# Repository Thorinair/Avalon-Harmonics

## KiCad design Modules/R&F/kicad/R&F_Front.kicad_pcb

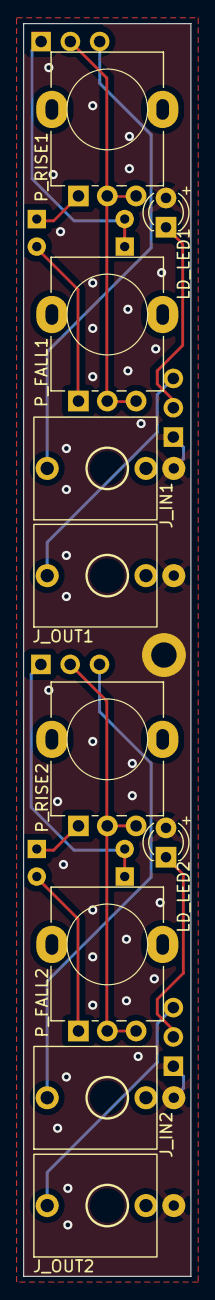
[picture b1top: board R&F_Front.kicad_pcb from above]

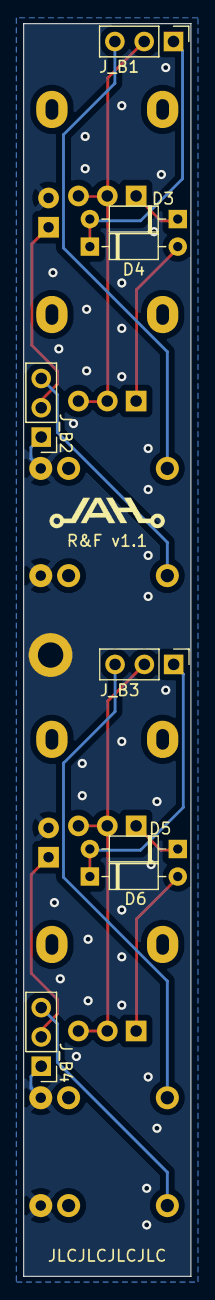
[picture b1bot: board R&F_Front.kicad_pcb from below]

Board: 2 copper layers, 14.5 x 108.6 mm, 18 parts (8 on the bottom side), 15 nets.

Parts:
D3, D4, D5, D6: 1N4148; D_DO-35_SOD27_P7.62mm_Horizontal
J_B1, J_B2, J_B3, J_B4: Conn_01x03_Female; PinHeader_1x03_P2.54mm_Vertical
J_IN1, J_IN2: PJ301M-12
J_OUT1, J_OUT2: PJ301M-12
LD_LED1, LD_LED2: LED (Bi); LED_D3.0mm_FlatTop
P_FALL1, P_FALL2: A1M; Potentiometer Alpha RD901F-40-00D
P_RISE1, P_RISE2: A1M; Potentiometer Alpha RD901F-40-00D

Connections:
GND: J_B2.1, J_B4.1, J_IN1.GND, J_IN2.GND, J_OUT1.GND, J_OUT2.GND, LD_LED1.2 (A), LD_LED2.2 (A)
unnamed: D3.1 (K), P_RISE1.1
unnamed: D3.2 (A), D4.1 (K), J_B1.1
unnamed: D4.2 (A), P_FALL1.1
unnamed: D5.1 (K), P_RISE2.1
unnamed: D5.2 (A), D6.1 (K), J_B3.1
unnamed: D6.2 (A), P_FALL2.1
unnamed: J_B1.2, P_FALL1.2, P_FALL1.3, P_RISE1.2, P_RISE1.3
unnamed: J_B1.3, J_IN1.SIG
unnamed: J_B2.2, LD_LED1.1 (K)
unnamed: J_B2.3, J_OUT1.SIG
unnamed: J_B3.2, P_FALL2.2, P_FALL2.3, P_RISE2.2, P_RISE2.3
unnamed: J_B3.3, J_IN2.SIG
unnamed: J_B4.2, LD_LED2.1 (K)
unnamed: J_B4.3, J_OUT2.SIG

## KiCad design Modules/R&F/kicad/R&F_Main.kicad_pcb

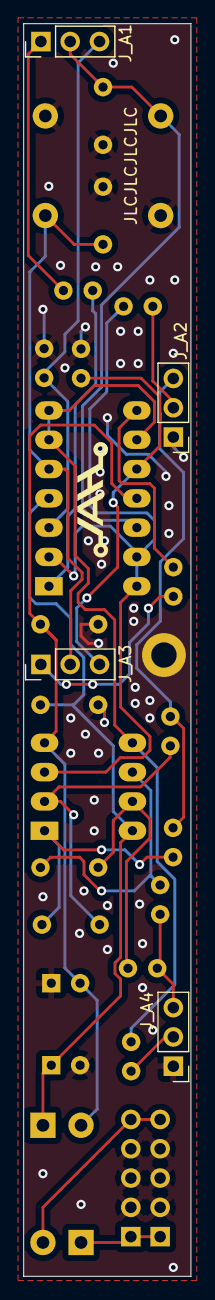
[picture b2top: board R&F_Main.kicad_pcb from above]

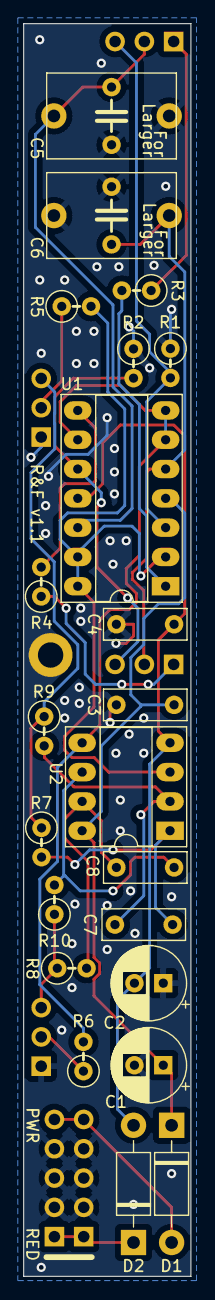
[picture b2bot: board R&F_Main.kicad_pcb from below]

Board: 2 copper layers, 14.5 x 108.6 mm, 27 parts (23 on the bottom side), 23 nets.

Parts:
C1, C2: 47uF; CP_Radial_D6.3mm_P2.50mm
C3, C4: 0.1uF; C_Disc_D7.0mm_W2.5mm_P5.00mm
C5, C6: 10uF (Film); C_Rect_L7.2mm_W11.0mm_P5.00mm_FKS2_FKP2_MKS2_MKP2_DUAL_SIZE
C7, C8: 100pF; C_Disc_D7.0mm_W2.5mm_P5.00mm
D1, D2: 1N4001; D_DO-41_SOD81_P10.16mm_Horizontal
J_A1, J_A2, J_A3, J_A4: Conn_01x03_Male; PinHeader_1x03_P2.54mm_Vertical
PWR1: PWR_10_Pin; Eurorack Power 10 Pin
R1, R2: 100k; R_Axial_DIN0207_L6.3mm_D2.5mm_P2.54mm_Vertical
R3, R4: 330; R_Axial_DIN0207_L6.3mm_D2.5mm_P2.54mm_Vertical
R5, R6, R7, R8: 1k; R_Axial_DIN0207_L6.3mm_D2.5mm_P2.54mm_Vertical
R9, R10: 4.7k; R_Axial_DIN0207_L6.3mm_D2.5mm_P2.54mm_Vertical
U1: TL074; DIP-14_W7.62mm_Socket_LongPads
U2: TL072; DIP-8_W7.62mm_Socket_LongPads

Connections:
+12V: C1.1, C3.1, D1.1 (K), U1.4 (V+), U2.8 (V+)
-12V: C2.2, C4.2, D2.2 (A), U1.11 (V-), U2.4 (V-)
/LED1: J_A2.2, R5.1
/LED2: J_A4.2, R6.1
/OUT1: J_A2.3, R7.1, R9.1
/OUT2: J_A4.3, R8.1, R10.1
/POT1_OUT: J_A1.1, R3.1
/POT2_OUT: J_A3.1, R4.1
GND: C1.2, C2.1, C3.2, C4.1, C5.2, C6.2, J_A2.1, J_A4.1, PWR1.2 (GND), R1.1, R2.1
unnamed: C5.1, J_A1.2, U1.12 (+)
unnamed: C6.1, J_A3.2, U1.5 (+)
unnamed: C7.1, R9.2, U2.2 (-)
unnamed: C7.2, R7.2, U2.1
unnamed: C8.1, R10.2, U2.6 (-)
unnamed: C8.2, R8.2, U2.7
unnamed: D1.2 (A), PWR1.1 (+12V)
unnamed: D2.1 (K), PWR1.3 (-12V)
unnamed: J_A1.3, R1.2, U1.3 (+)
unnamed: J_A3.3, R2.2, U1.10 (+)
unnamed: R3.2, U1.1
unnamed: R4.2, U1.8
unnamed: R5.2, U1.2 (-), U1.13 (-), U1.14, U2.3 (+)
unnamed: R6.2, U1.6 (-), U1.7, U1.9 (-), U2.5 (+)

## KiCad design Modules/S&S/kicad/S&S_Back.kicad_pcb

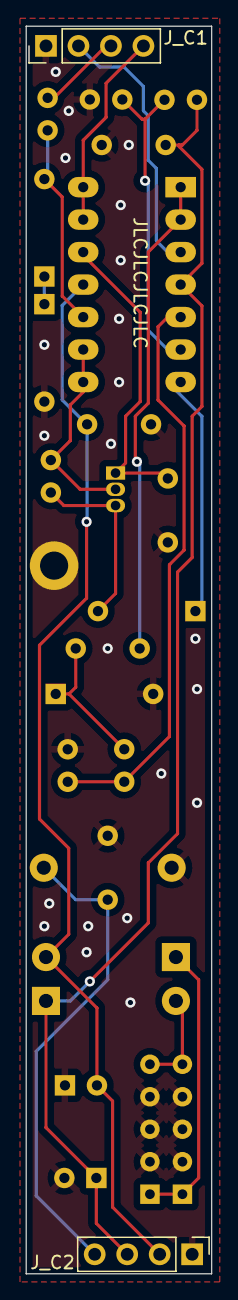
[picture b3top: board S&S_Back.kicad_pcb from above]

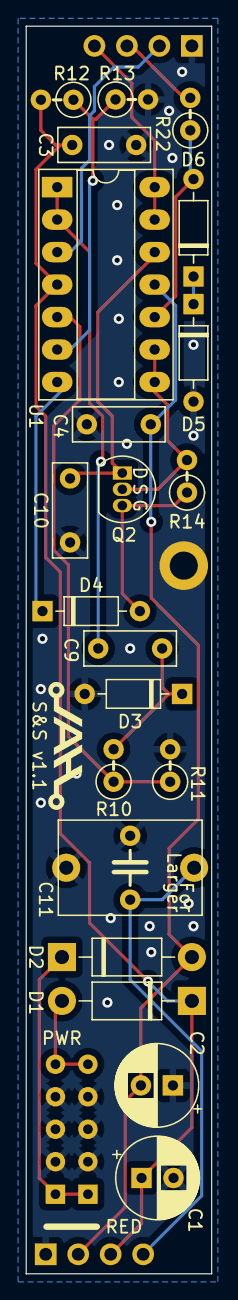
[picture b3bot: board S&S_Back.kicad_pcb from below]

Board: 2 copper layers, 14.5 x 97.6 mm, 24 parts (22 on the bottom side), 19 nets.

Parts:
C1, C2: 47uF; CP_Radial_D6.3mm_P2.50mm
C3, C4: 0.1uF; C_Disc_D7.0mm_W2.5mm_P5.00mm
C9: 100pF; C_Disc_D7.0mm_W2.5mm_P5.00mm
C10: 10nF (Film); C_Rect_L7.2mm_W2.5mm_P5.00mm_FKS2_FKP2_MKS2_MKP2
C11: 2.2uF (Film); C_Rect_L7.2mm_W11.0mm_P5.00mm_FKS2_FKP2_MKS2_MKP2_DUAL_SIZE
D1, D2: 1N4001; D_DO-41_SOD81_P10.16mm_Horizontal
D3, D4, D5: 1N4148; D_DO-35_SOD27_P7.62mm_Horizontal
D6: 4.7V; D_DO-35_SOD27_P7.62mm_Horizontal
J_C1, J_C2: Conn_01x04_Male; PinHeader_1x04_P2.54mm_Vertical
PWR1: PWR_10_Pin; Eurorack Power 10 Pin
Q2: J112; TO-92_Inline
R10, R11: 33k; R_Axial_DIN0207_L6.3mm_D2.5mm_P2.54mm_Vertical
R12, R14: 1M; R_Axial_DIN0207_L6.3mm_D2.5mm_P2.54mm_Vertical
R13: 47k; R_Axial_DIN0207_L6.3mm_D2.5mm_P2.54mm_Vertical
R22: 10k; R_Axial_DIN0207_L6.3mm_D2.5mm_P2.54mm_Vertical
U1: TL074; DIP-14_W7.62mm_Socket_LongPads

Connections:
+12V: C1.1, C3.1, D1.1 (K), J_C2.3, R12.2, U1.4 (V+)
-12V: C2.2, C4.2, D2.2 (A), J_C2.2, U1.11 (V-)
/S_H1: J_C1.4, U1.13 (-), U1.14
GND: C1.2, C2.1, C3.2, C4.1, C10.1, C11.2, D3.2 (A), D5.2 (A), J_C1.1, J_C2.1, PWR1.2 (GND), R11.2, R13.2
unnamed: C9.1, U1.1, U1.2 (-)
unnamed: C9.2, D3.1 (K), R10.2
unnamed: C10.2, Q2.1 (D), U1.12 (+)
unnamed: C11.1, J_C2.4
unnamed: D1.2 (A), PWR1.1 (+12V)
unnamed: D2.1 (K), PWR1.3 (-12V)
unnamed: D4.1 (K), U1.7
unnamed: D4.2 (A), Q2.3 (G), R14.1
unnamed: D5.1 (K), D6.1 (K)
unnamed: J_C1.2, U1.3 (+)
unnamed: J_C1.3, R22.2
unnamed: Q2.2 (S), R14.2, U1.8, U1.9 (-)
unnamed: R10.1, R11.1, U1.5 (+)
unnamed: R12.1, R13.1, U1.6 (-)
unnamed: D6.2 (A), R22.1, U1.10 (+)

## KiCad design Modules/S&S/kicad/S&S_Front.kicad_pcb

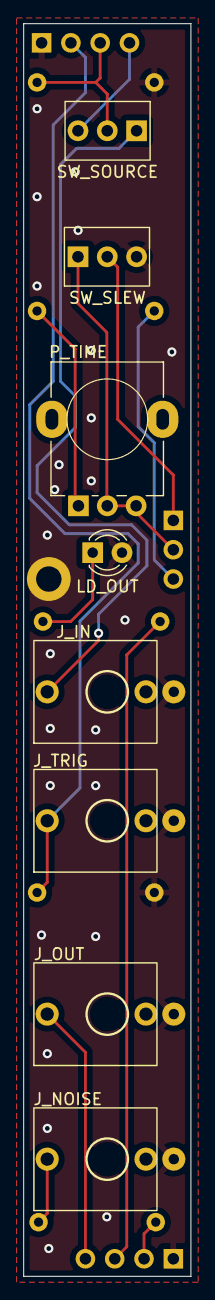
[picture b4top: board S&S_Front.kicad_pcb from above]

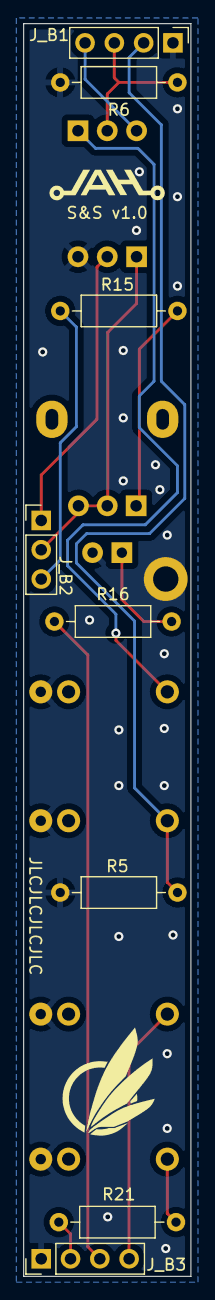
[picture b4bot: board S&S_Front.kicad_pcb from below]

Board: 2 copper layers, 14.5 x 108.6 mm, 16 parts (8 on the bottom side), 14 nets.

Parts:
J_B1, J_B3: Conn_01x04_Female; PinHeader_1x04_P2.54mm_Vertical
J_B2: Conn_01x03_Female; PinHeader_1x03_P2.54mm_Vertical
J_IN1: PJ301M-12
J_NOISE1: PJ301M-12
J_OUT1: PJ301M-12
J_TRIG1: PJ301M-12
LD_OUT1: LED (Bi); LED_D3.0mm_FlatTop
P_TIME1: A1M; Potentiometer Alpha RD901F-40-00D
R5, R6: 100k; R_Axial_DIN0207_L6.3mm_D2.5mm_P10.16mm_Horizontal
R15: 330; R_Axial_DIN0207_L6.3mm_D2.5mm_P10.16mm_Horizontal
R16, R21: 1k; R_Axial_DIN0207_L6.3mm_D2.5mm_P10.16mm_Horizontal
SW_SLEW1: SW_SPDT; SPDT
SW_SOURCE1: SW_SPDT; SPDT

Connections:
GND: J_B1.1, J_B3.1, J_IN1.GND, J_NOISE1.GND, J_OUT1.GND, J_TRIG1.GND, LD_OUT1.2 (A), R5.2, R6.2, SW_SLEW1.3 (C)
unnamed: J_B1.2, J_TRIG1.SIG, R5.1
unnamed: J_B1.3, R6.1, SW_SOURCE1.2 (B)
unnamed: J_B1.4, SW_SOURCE1.3 (C)
unnamed: J_B2.1, SW_SLEW1.2 (B)
unnamed: J_B2.2, P_TIME1.2, P_TIME1.3, SW_SLEW1.1 (A)
unnamed: J_B2.3, R15.2
unnamed: J_B3.2, R21.2
unnamed: J_B3.3, R16.1
unnamed: J_B3.4, J_OUT1.SIG
unnamed: J_IN1.SIG, SW_SOURCE1.1 (A)
unnamed: J_NOISE1.SIG, R21.1
unnamed: LD_OUT1.1 (K), R16.2
unnamed: P_TIME1.1, R15.1

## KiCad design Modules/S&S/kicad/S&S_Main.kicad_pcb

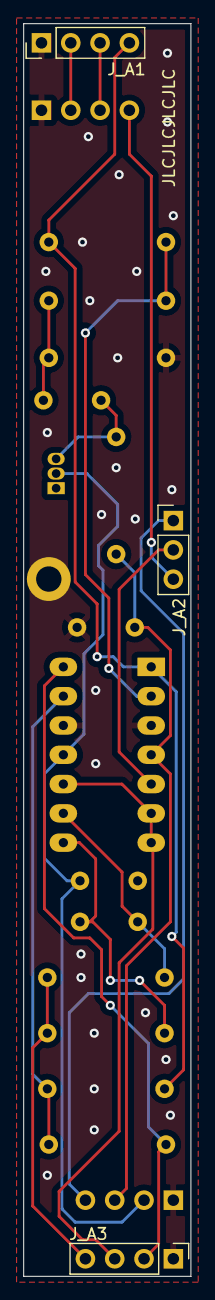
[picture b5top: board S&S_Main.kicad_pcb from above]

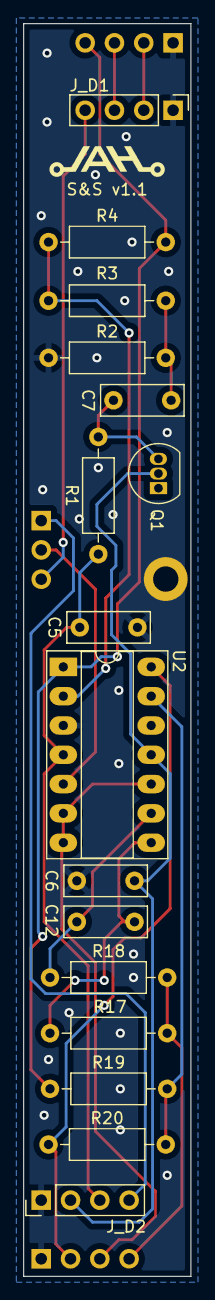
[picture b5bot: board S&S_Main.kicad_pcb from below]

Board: 2 copper layers, 14.5 x 108.6 mm, 19 parts (16 on the bottom side), 18 nets.

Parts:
C5, C6, C7: 0.1uF; C_Disc_D7.0mm_W2.5mm_P5.00mm
C12: 100pF; C_Disc_D7.0mm_W2.5mm_P5.00mm
J_A1, J_A3: Conn_01x04_Male; PinHeader_1x04_P2.54mm_Vertical
J_A2: Conn_01x03_Male; PinHeader_1x03_P2.54mm_Vertical
J_D1, J_D2: Conn_01x04_Female; PinHeader_1x04_P2.54mm_Vertical
Q1: BC547; TO-92_Inline
R1: 240k; R_Axial_DIN0207_L6.3mm_D2.5mm_P10.16mm_Horizontal
R2, R4: 1M; R_Axial_DIN0207_L6.3mm_D2.5mm_P10.16mm_Horizontal
R3: 2.2k; R_Axial_DIN0207_L6.3mm_D2.5mm_P10.16mm_Horizontal
R17: 1k; R_Axial_DIN0207_L6.3mm_D2.5mm_P10.16mm_Horizontal
R18: 4.7k; R_Axial_DIN0207_L6.3mm_D2.5mm_P10.16mm_Horizontal
R19: 47k; R_Axial_DIN0207_L6.3mm_D2.5mm_P10.16mm_Horizontal
R20: 33k; R_Axial_DIN0207_L6.3mm_D2.5mm_P10.16mm_Horizontal
U2: TL074; DIP-14_W7.62mm_Socket_LongPads

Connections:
+12V: C5.1, J_D2.3, R1.2, U2.4 (V+)
-12V: C6.2, J_D2.2, Q1.2 (B), U2.11 (V-)
/CAP: J_A2.1, J_D2.4
/NOISE: J_A1.4, R4.1, R19.2, U2.1
/S_H2: J_A2.3, J_D1.4
GND: C5.2, C6.1, J_A1.1, J_A3.1, J_D1.1, J_D2.1, R2.2, U2.3 (+), U2.12 (+)
unnamed: C7.1, Q1.3 (E), R1.1
unnamed: C7.2, R2.1, R3.2
unnamed: C12.1, R18.2, U2.9 (-)
unnamed: C12.2, R17.2, U2.8
unnamed: J_A1.2, J_D1.2
unnamed: J_A1.3, J_D1.3
unnamed: J_A2.2, U2.5 (+)
unnamed: J_A3.2, R20.1, U2.14
unnamed: J_A3.3, U2.6 (-), U2.7, U2.10 (+)
unnamed: J_A3.4, R17.1, R18.1
unnamed: R3.1, R4.2, U2.2 (-)
unnamed: R19.1, R20.2, U2.13 (-)
